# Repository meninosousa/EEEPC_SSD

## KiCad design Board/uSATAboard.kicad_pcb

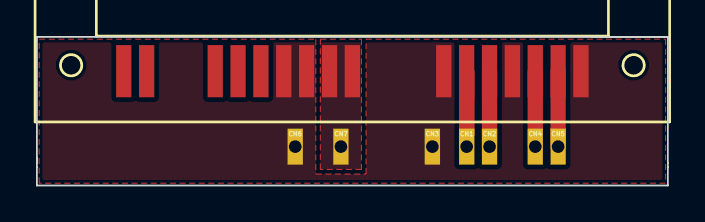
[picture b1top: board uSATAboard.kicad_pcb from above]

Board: 2 copper layers, 35.1 x 8.3 mm, 8 parts (0 on the bottom side), 6 nets.

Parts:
CN1: B+; CONN1
CN2: B-; CONN1
CN3, CN6: GND; CONN1
CN4: A-; CONN1
CN5: A+; CONN1
CN7: +3.3V; CONN1
CN8: USATA; uSATA

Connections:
+3.3V: CN7.1, CN8.8, CN8.9
A+: CN5.1, CN8.2
A-: CN4.1, CN8.3
B+: CN1.1, CN8.6
B-: CN2.1, CN8.5
GND: CN3.1, CN6.1, CN8.1, CN8.4, CN8.7, CN8.10, CN8.11

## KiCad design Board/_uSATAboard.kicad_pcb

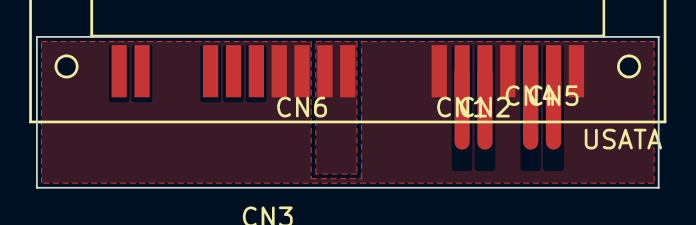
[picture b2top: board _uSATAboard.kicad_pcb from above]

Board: 2 copper layers, 34.5 x 8.4 mm, 8 parts (0 on the bottom side), 2 nets.

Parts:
CN1: B+; CONN1
CN2: B-; CONN1
CN3, CN6: GND; CONN1
CN4: A-; CONN1
CN5: A+; CONN1
CN7: +3.3V; CONN1
CN8: USATA; uSATA

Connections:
+3.3V: CN8.8, CN8.9
GND: CN8.1, CN8.4, CN8.7, CN8.10, CN8.11

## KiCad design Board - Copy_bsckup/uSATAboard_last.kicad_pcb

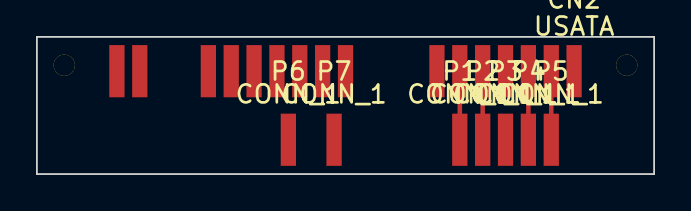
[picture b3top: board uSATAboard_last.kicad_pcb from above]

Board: 2 copper layers, 34.3 x 7.6 mm, 8 parts (0 on the bottom side), 6 nets.

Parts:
CN2: USATA; uSATA
P1, P2, P3, P4, P5, P6, P7: CONN_1; smd_usata

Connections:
/+3.3V: CN2.8, CN2.9, P7.1
/A+: CN2.2, P5.1
/A-: CN2.3, P4.1
/B+: CN2.6, P1.1
/B-: CN2.5, P2.1
/GND: CN2.1, CN2.4, CN2.7, CN2.10, CN2.11, P3.1, P6.1

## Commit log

2016-06-11 :circus_tent: Added .gitattributes & .gitignore files
2016-06-14 final
    for now
2016-06-15 datasheets
    pls
2016-06-20 to repeat
    done
2016-06-20 one more
    pls
2016-12-20 do it
    done
